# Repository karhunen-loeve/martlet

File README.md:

# martlet
Ergogen designed minimalist keyboard 

The Martlet is intended to be a minimalist keyboard that I plan to use primarily for traveling. I've previously used a low-profile Corne keyboard (42 keys). For this reason, the Martlet is intended to be based on the Corne design. The main difference is that it won't be a split design, and the keyboard will be wireless. Essentially, both halves of the Corne will be glued together. I might adjust the position of the little finger keys a bit to suit my anatomy.

# Key Features

- Wireless
- Similar to corne layout
- 42 Keys (Maybe only 40 Keys)
- More staggered pinky colmn
- No RGB lights
- No Frills

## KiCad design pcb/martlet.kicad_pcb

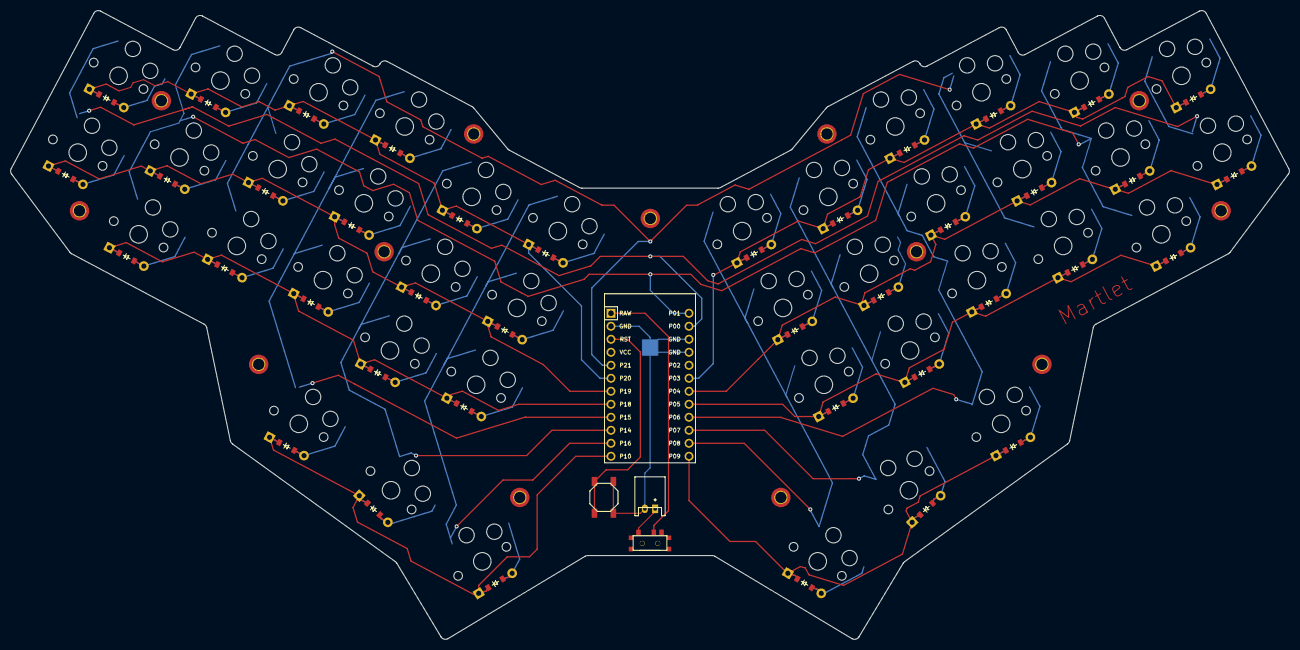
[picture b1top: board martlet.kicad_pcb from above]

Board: 2 copper layers, 249.8 x 122.8 mm, 84 parts (0 on the bottom side), 61 nets.

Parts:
B1: SW_TACT_ALPS_SKQGABE010
D1, D2, D3, D4, D5, D6, D7, D8, D9, D10, D11, D12, D13, D14, D15, D16, D17, D18, D19, D20, D21, D22, D23, D24, D25, D26, D27, D28, D29, D30, D31, D32, D33, D34, D35, D36, D37, D38, D39, D40: ComboDiode
JST1: JST_PH_S2B-PH-K_02x2.00mm_Angled
MCU1: ProMicro
S1, S2, S3, S4, S5, S6, S7, S8, S9, S10, S11, S12, S13, S14, S15, S16, S17, S18, S19, S20, S21, S22, S23, S24, S25, S26, S27, S28, S29, S30, S31, S32, S33, S34, S35, S36, S37, S38, S39, S40: PG1350
T1: SPDT_C128955

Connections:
GND: B1.1, JST1.2, MCU1.2, MCU1.15, MCU1.16
P0: MCU1.14, S1.1, S2.1, S21.1, S22.1
P1: MCU1.13, S3.1, S4.1, S5.1, S23.1, S24.1, S25.1
P3: D22.1, D25.1, D28.1, D31.1, D34.1, D37.1, MCU1.18
P4: D21.1, D24.1, D27.1, D30.1, D33.1, D36.1, MCU1.19
P5: D23.1, D26.1, D29.1, D32.1, D35.1, MCU1.20
P6: MCU1.21, S29.1, S30.1, S31.1, S38.1
P7: MCU1.22, S32.1, S33.1, S34.1, S39.1
P8: MCU1.23, S35.1, S36.1, S37.1, S40.1
P9: D38.1, D39.1, D40.1, MCU1.24
P10: D18.1, D19.1, D20.1, MCU1.12
P14: MCU1.10, S12.1, S13.1, S14.1, S19.1
P15: MCU1.9, S9.1, S10.1, S11.1, S18.1
P16: MCU1.11, S15.1, S16.1, S17.1, S20.1
P18: D3.1, D6.1, D9.1, D12.1, D15.1, MCU1.8
P19: D1.1, D4.1, D7.1, D10.1, D13.1, D16.1, MCU1.7
P20: D2.1, D5.1, D8.1, D11.1, D14.1, D17.1, MCU1.6
P21: MCU1.5, S6.1, S7.1, S8.1, S26.1, S27.1, S28.1
RAW: MCU1.1, T1.2
RST: B1.2, MCU1.3
index_bottom: D12.2, S12.2
index_home: D13.2, S13.2
index_top: D14.2, S14.2
inner_bottom: D15.2, S15.2
inner_home: D16.2, S16.2
inner_top: D17.2, S17.2
left_cluster: D18.2, S18.2
middle_bottom: D9.2, S9.2
middle_cluster: D19.2, S19.2
middle_home: D10.2, S10.2
middle_top: D11.2, S11.2
mirror_index_bottom: D32.2, S32.2
mirror_index_home: D33.2, S33.2
mirror_index_top: D34.2, S34.2
mirror_inner_bottom: D35.2, S35.2
mirror_inner_home: D36.2, S36.2
mirror_inner_top: D37.2, S37.2
mirror_left_cluster: D38.2, S38.2
mirror_middle_bottom: D29.2, S29.2
mirror_middle_cluster: D39.2, S39.2
mirror_middle_home: D30.2, S30.2
mirror_middle_top: D31.2, S31.2
mirror_outer_home: D21.2, S21.2
mirror_outer_top: D22.2, S22.2
mirror_pinky_bottom: D23.2, S23.2
mirror_pinky_home: D24.2, S24.2
mirror_pinky_top: D25.2, S25.2
mirror_right_cluster: D40.2, S40.2
mirror_ring_bottom: D26.2, S26.2
mirror_ring_home: D27.2, S27.2
mirror_ring_top: D28.2, S28.2
outer_home: D1.2, S1.2
outer_top: D2.2, S2.2
pinky_bottom: D3.2, S3.2
pinky_home: D4.2, S4.2
pinky_top: D5.2, S5.2
pos: JST1.1, T1.1
right_cluster: D20.2, S20.2
ring_bottom: D6.2, S6.2
ring_home: D7.2, S7.2
ring_top: D8.2, S8.2

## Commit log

2025-05-15 Create initial thougts in Readme file
2025-05-15 create a first ergogen sketch in order to get used to ergogens configurator
2025-05-16 create a corne like key layout
2025-05-16 adjust layout and add mirrored right side
2025-05-17 create a first ergogen outline
2025-05-18 fix readme: The martlet will probably have only 40 Keys
2025-05-18 adjust ergogen outline to match more the contour of the keys.
2025-05-18 finish board outline (for now)
2025-05-20 add row and column net information for the pcb layout
2025-05-20 fix row_net pin names
2025-05-23 add slider, reset button and battery connector to pcb
2025-05-24 change column and row net in order to optimize kicad-lines
2025-05-24 fix row 6 pin connection
2025-05-27 fix row 2 pin connection
2025-06-11 add kicad file
    The file contains:
    - the actual routing
    - vias
    - mounting holes (M2)
    - `Martlet` title
2025-06-11 adjust "Martlet" title on the front of the pcb/martlet
    Remark: This is the design I ordered the pcb
